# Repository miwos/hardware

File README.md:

# MIWOS Hardware

## BOM

| Qty | Value          | Device         | Package                    | Parts                                                         | Description                                                                           |
| --- | -------------- | -------------- | -------------------------- | ------------------------------------------------------------- | ------------------------------------------------------------------------------------- |
| 2   |                | DIODE-SOD123   | SOD123                     | D1, D2                                                        | DIODE                                                                                 |
| 7   |                | LED3MM         | LED3MM                     | LED1, LED2, LED3, LED4, LED5, LED6, LED7                      | LED                                                                                   |
| 2   | 0.1uF          | C-EUC0603      | C0603                      | C1, C2                                                        | CAPACITOR, European symbol                                                            |
| 2   | 220R           | R-EU_R0603     | R0603                      | R3, R8                                                        | RESISTOR, European symbol                                                             |
| 4   | 35RASMT2BHNTRX | 35RASMT2BHNTRX | SWITCHCRAFT_35RASMT2BHNTRX | MIDI1-IN, MIDI1-OUT, MIDI2-IN, MIDI2-OUT                      | Conn 3.5MM Stereo Jack F 3 POS Solder RA SMD 3 Terminal 1 Port T/R Check availability |
| 9   | 470R           | R-EU_R0603     | R0603                      | R2, R5, R10, R19, R20, R21, R22, R23, R24                     | RESISTOR, European symbol                                                             |
| 4   | 47R            | R-EU_R0603     | R0603                      | R1, R4, R9, R11                                               | RESISTOR, European symbol                                                             |
| 1   | 614004190021   | 614004190021   | 614004190021               | USB-HUB                                                       | USB TYPE A UP RIGHT THT - SHORT TYPE=>ConUSB2 614004190021                            |
| 2   | 6N138          | 6N138          | DIP08-SMD                  | OK1, OK2                                                      |                                                                                       |
| 7   | D6R60F1LFS     | D6R60F1LFS     | D6R                        | BUTTON1, BUTTON2, BUTTON3, BUTTON4, BUTTON5, BUTTON6, BUTTON7 | Pushbutton Switch SPST-NO Keyswitch Through Hole Check prices                         |
| 3   | DFR0647        | DFR0647        | DFR0647                    | DISPLAY1, DISPLAY2, DISPLAY3                                  |                                                                                       |
| 4   | MOUNT_CH       | MOUNT_CH       | MOUNT_CH32                 | P1, P2, P3, P4                                                | mounting hole                                                                         |
| 3   | PEC16          | PEC16          | PEC16                      | ENCODER1, ENCODER2, ENCODER3                                  | Encoder 12mm 0detents 20mm Shft Push Momentry Sw 24 Pulse Check prices                |
| 1   | TEENSY4.1      | TEENSY4.1      | TEENSY4.1                  | TEENSY-41                                                     |                                                                                       |

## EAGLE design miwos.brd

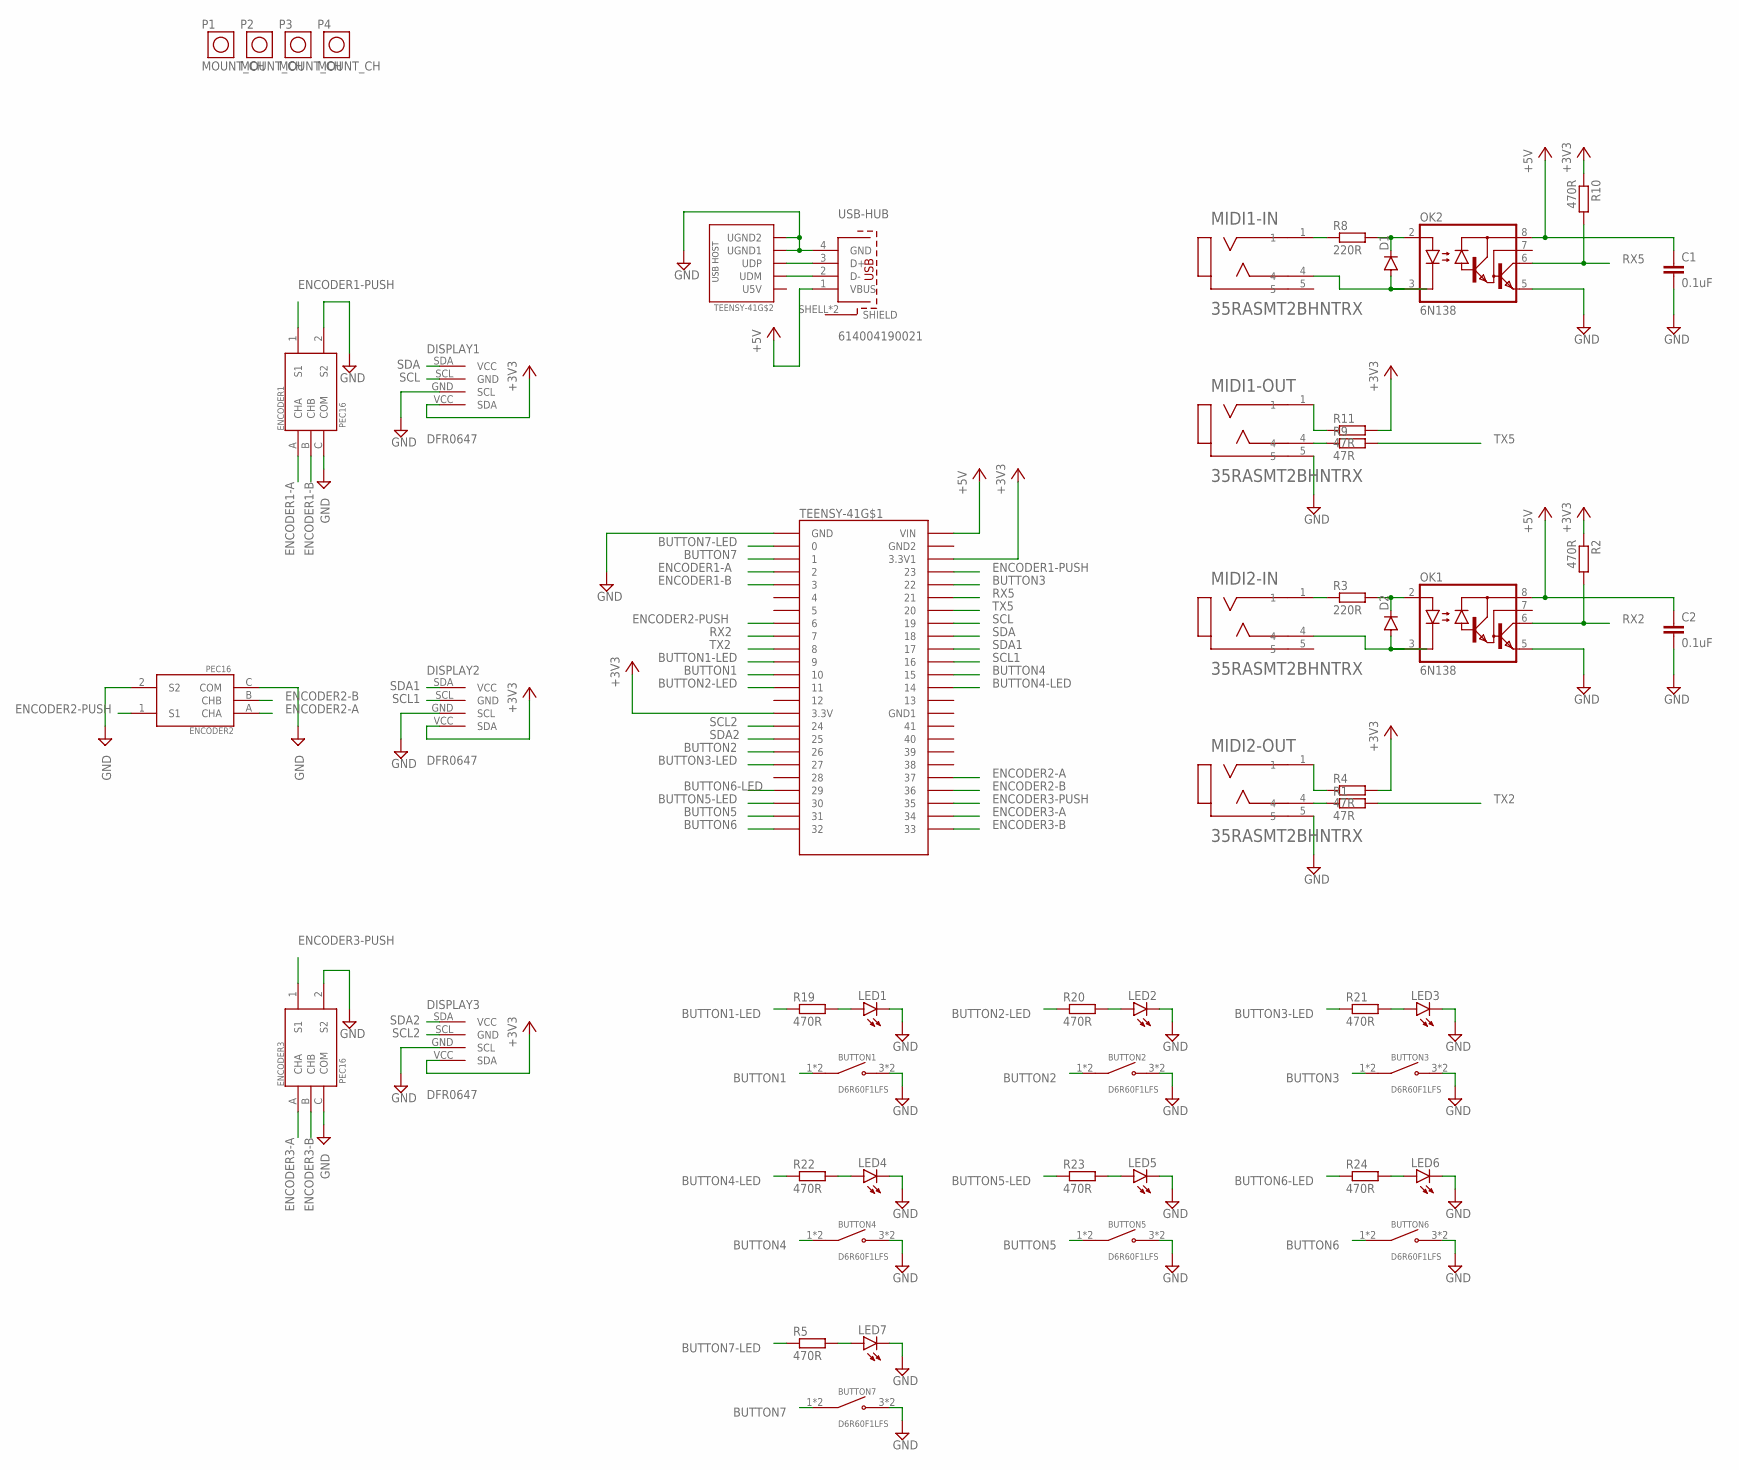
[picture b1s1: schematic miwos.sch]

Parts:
BUTTON1, BUTTON2, BUTTON3, BUTTON4, BUTTON5, BUTTON6, BUTTON7: D6R60F1LFS; D6R
C1, C2: 0.1uF; C0603
D1, D2: DIODE-SOD123; SOD123
DISPLAY1, DISPLAY2, DISPLAY3: DFR0647
ENCODER1, ENCODER2, ENCODER3: PEC16
LED1, LED2, LED3, LED4, LED5, LED6, LED7: LED3MM
MIDI1-IN, MIDI1-OUT, MIDI2-IN, MIDI2-OUT: 35RASMT2BHNTRX; SWITCHCRAFT_35RASMT2BHNTRX
OK1, OK2: 6N138; DIP08-SMD
P1, P2, P3, P4: MOUNT_CH; MOUNT_CH32
R1, R4, R9, R11: 47R; R0603
R2, R5, R10, R19, R20, R21, R22, R23, R24: 470R; R0603
R3, R8: 220R; R0603
TEENSY-41: TEENSY4.1
USB-HUB: 614004190021

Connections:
+3V3: DISPLAY1.VCC (SDA), DISPLAY2.VCC (SDA), DISPLAY3.VCC (SDA), R2.1, R4.2, R10.1, R11.2, TEENSY-41.3V3 (3.3V), TEENSY-41.3V3_LO (3.3V1)
+5V: C1.1, C2.1, OK1.8 (VCC), OK2.8 (VCC), TEENSY-41.VIN, USB-HUB.1 (VBUS)
BUTTON1: BUTTON1.1 (COM), BUTTON1.2 (COM), TEENSY-41.10/CS (10)
BUTTON1-LED: R19.1, TEENSY-41.9
BUTTON2: BUTTON2.1 (COM), BUTTON2.2 (COM), TEENSY-41.26
BUTTON2-LED: R20.1, TEENSY-41.11/MOSI (11)
BUTTON3: BUTTON3.1 (COM), BUTTON3.2 (COM), TEENSY-41.22/A8 (22)
BUTTON3-LED: R21.1, TEENSY-41.27
BUTTON4: BUTTON4.1 (COM), BUTTON4.2 (COM), TEENSY-41.15/A1 (15)
BUTTON4-LED: R22.1, TEENSY-41.14/A0 (14)
BUTTON5: BUTTON5.1 (COM), BUTTON5.2 (COM), TEENSY-41.31/A12 (31)
BUTTON5-LED: R23.1, TEENSY-41.30
BUTTON6: BUTTON6.1 (COM), BUTTON6.2 (COM), TEENSY-41.32
BUTTON6-LED: R24.1, TEENSY-41.29
BUTTON7: BUTTON7.1 (COM), BUTTON7.2 (COM), TEENSY-41.1/TX (1)
BUTTON7-LED: R5.1, TEENSY-41.0/RX (0)
ENCODER1-A: ENCODER1.A (CHA), TEENSY-41.2
ENCODER1-B: ENCODER1.B (CHB), TEENSY-41.3
ENCODER1-PUSH: ENCODER1.1 (S1), TEENSY-41.23/A9 (23)
ENCODER2-A: ENCODER2.A (CHA), TEENSY-41.37
ENCODER2-B: ENCODER2.B (CHB), TEENSY-41.36
ENCODER2-PUSH: ENCODER2.1 (S1), TEENSY-41.6
ENCODER3-A: ENCODER3.A (CHA), TEENSY-41.34
ENCODER3-B: ENCODER3.B (CHB), TEENSY-41.33
ENCODER3-PUSH: ENCODER3.1 (S1), TEENSY-41.35
GND: BUTTON1.3 (NO), BUTTON1.4 (NO), BUTTON2.3 (NO), BUTTON2.4 (NO), BUTTON3.3 (NO), BUTTON3.4 (NO), BUTTON4.3 (NO), BUTTON4.4 (NO), BUTTON5.3 (NO), BUTTON5.4 (NO), BUTTON6.3 (NO), BUTTON6.4 (NO), BUTTON7.3 (NO), BUTTON7.4 (NO), C1.2, C2.2, DISPLAY1.GND (SCL), DISPLAY2.GND (SCL), DISPLAY3.GND (SCL), ENCODER1.2 (S2), ENCODER1.C (COM), ENCODER2.2 (S2), ENCODER2.C (COM), ENCODER3.2 (S2), ENCODER3.C (COM), LED1.K (C), LED2.K (C), LED3.K (C), LED4.K (C), LED5.K (C), LED6.K (C), LED7.K (C), MIDI1-OUT.5, MIDI2-OUT.5, OK1.5 (GND), OK2.5 (GND), TEENSY-41.GND, TEENSY-41.GND-U1 (UGND1), TEENSY-41.GND-U2 (UGND2), USB-HUB.4 (GND)
unnamed: TEENSY-41.UD- (UDM), USB-HUB.2 (D-)
unnamed: TEENSY-41.UD+ (UDP), USB-HUB.3 (D+)
unnamed: LED7.A, R5.2
unnamed: D1.C, OK2.2 (A), R8.2
unnamed: D1.A, MIDI1-IN.4, OK2.3 (C)
unnamed: MIDI1-IN.1, R8.1
unnamed: MIDI1-OUT.4, R9.1
unnamed: MIDI1-OUT.1, R11.1
unnamed: D2.C, OK1.2 (A), R3.2
unnamed: D2.A, MIDI2-IN.4, OK1.3 (C)
unnamed: MIDI2-IN.1, R3.1
unnamed: MIDI2-OUT.4, R1.1
unnamed: MIDI2-OUT.1, R4.1
unnamed: LED1.A, R19.2
unnamed: LED2.A, R20.2
unnamed: LED3.A, R21.2
unnamed: LED4.A, R22.2
unnamed: LED5.A, R23.2
unnamed: LED6.A, R24.2
RX2: OK1.6 (VO), R2.2, TEENSY-41.7
RX5: OK2.6 (VO), R10.2, TEENSY-41.21/A7 (21)
SCL: DISPLAY1.SCL (GND), TEENSY-41.19/A5/SCL (19)
SCL1: DISPLAY2.SCL (GND), TEENSY-41.16/A2 (16)
SCL2: DISPLAY3.SCL (GND), TEENSY-41.24
SDA: DISPLAY1.SDA (VCC), TEENSY-41.18/A4/SDA (18)
SDA1: DISPLAY2.SDA (VCC), TEENSY-41.17/A3 (17)
SDA2: DISPLAY3.SDA (VCC), TEENSY-41.25
TX2: R1.2, TEENSY-41.8
TX5: R9.2, TEENSY-41.20/A6 (20)

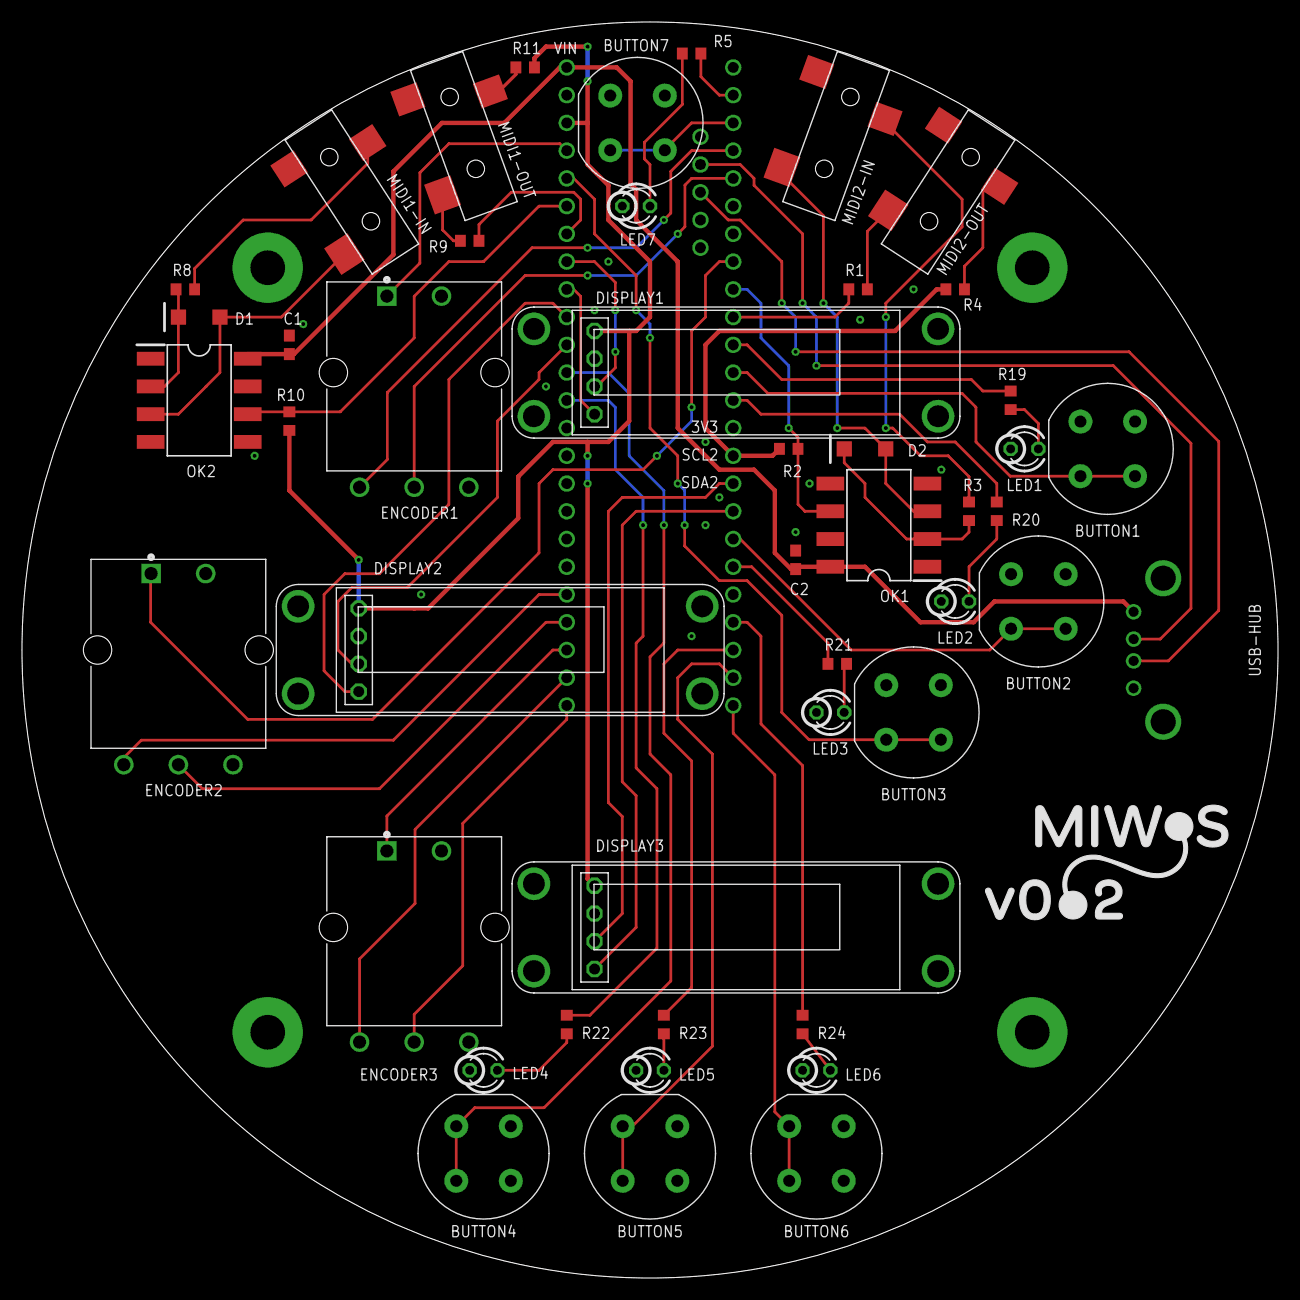
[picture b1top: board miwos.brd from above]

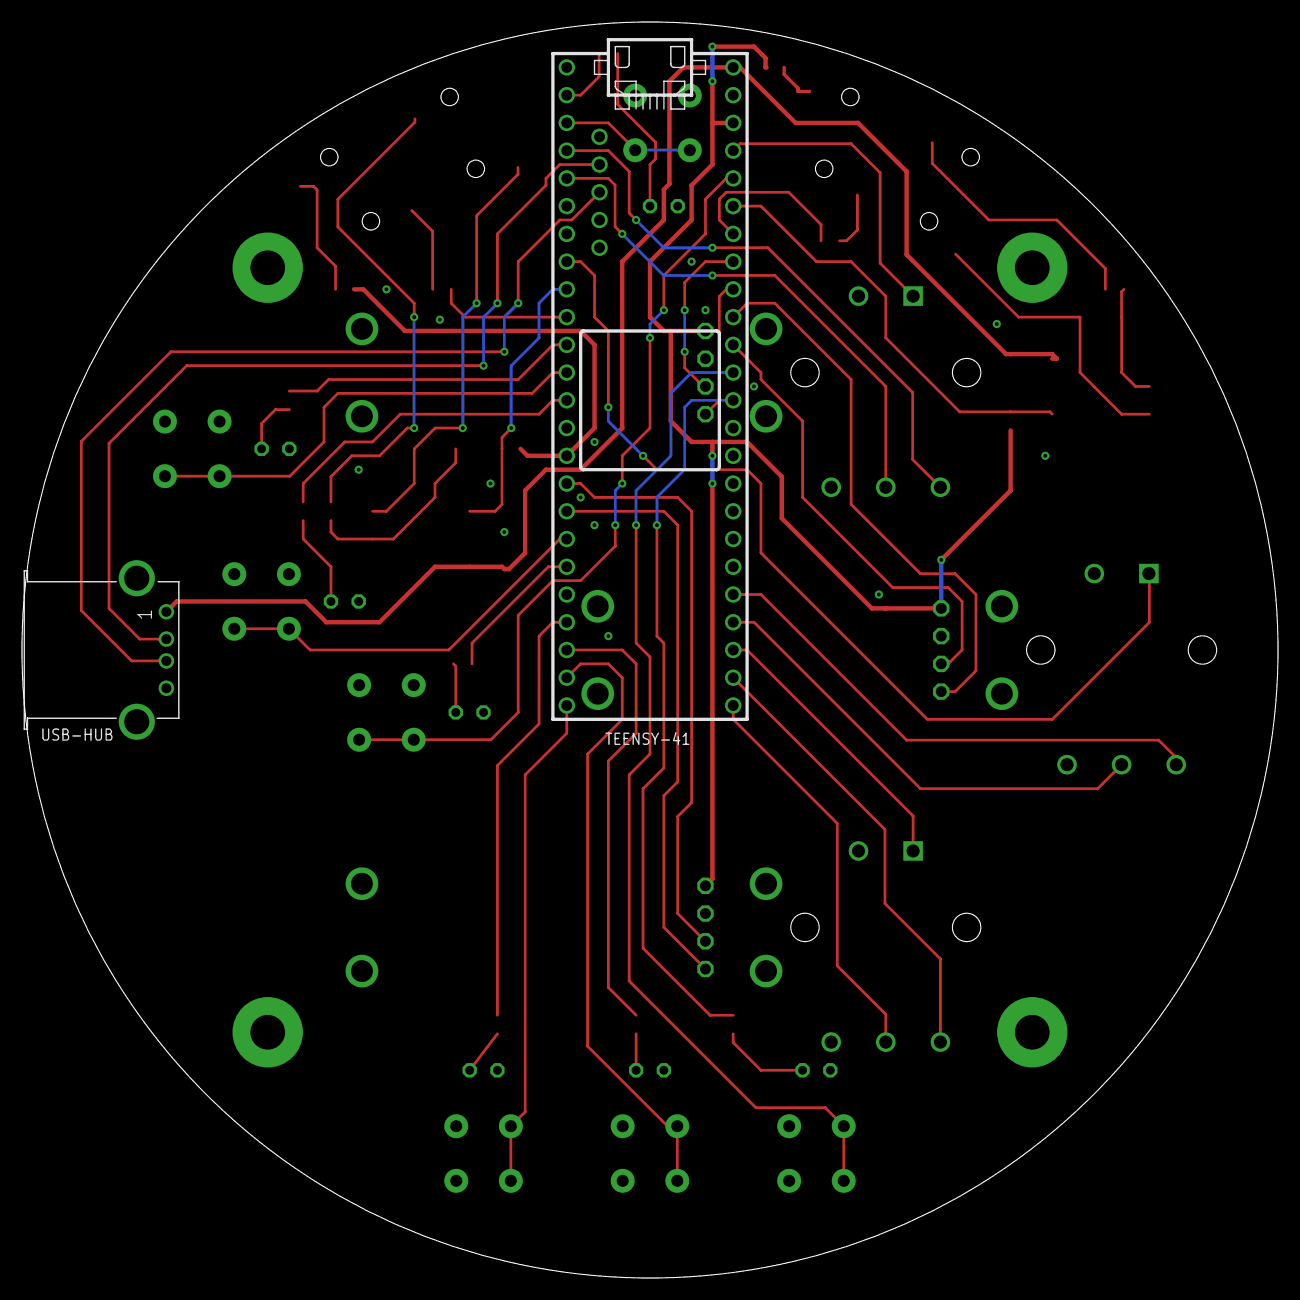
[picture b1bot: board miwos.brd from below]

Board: 2 copper layers, 115.0 x 115.0 mm, 51 parts (2 on the bottom side), 55 nets.

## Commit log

2021-12-06 Use lorenz's version
2021-12-06 Wire encoders
2021-12-10 Small fixes
2021-12-16 Refactor, add button LEDs
2021-12-17 Add encoder LEDs, don't wire them for now
2021-12-17 Wire encoder LEDs
2022-01-04 Use center origin, small fixes
2022-01-04 Place labels, small fixes
2022-01-04 Optimize ratsnest
2022-01-06 Fix DRC errors
2022-01-07 Small changes
2022-01-15 Small fixes, add logo
2022-01-17 Add gerber
2022-02-04 Add bom, fix #2
2022-03-15 Fix wrong encoder wiring
2022-03-15 Update to illuminated D6R buttons
2022-03-15 Rearrange midi jacks and encoders/displays
2022-03-16 Use DFR0647 displays
2022-03-18 Use 6N138 SMD footprint
2022-03-18 Add shift/menu button
2022-03-19 Update bom
2022-03-28 Use non-illuminated buttons, add mounting holes
2022-03-31 Various changes
2022-04-06 Use TRS midi
2022-04-11 Various changes, add mounting holes
2022-04-11 Rotate LEDs
2022-04-11 Add logo
2022-04-11 Cleanup
